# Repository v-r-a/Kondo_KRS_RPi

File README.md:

# Kondo_KRS_RPi
A Linux library for Raspberry Pi to operate the KRS motors (Kondo humanoid) using GPIO UART ports. 

Software dependencies: [wiringPi]([url](https://github.com/WiringPi/WiringPi)). wiringPi is needed for toggling RX/TX/En using the tri-state buffer.

Hardware dependencies: PCB for half-duplex communication with Kondo KRS 2552 motors.  The PCB designed is open-sourced here. However there are major changes in the PCB. A new version that is physically tested will be uploaded soon.

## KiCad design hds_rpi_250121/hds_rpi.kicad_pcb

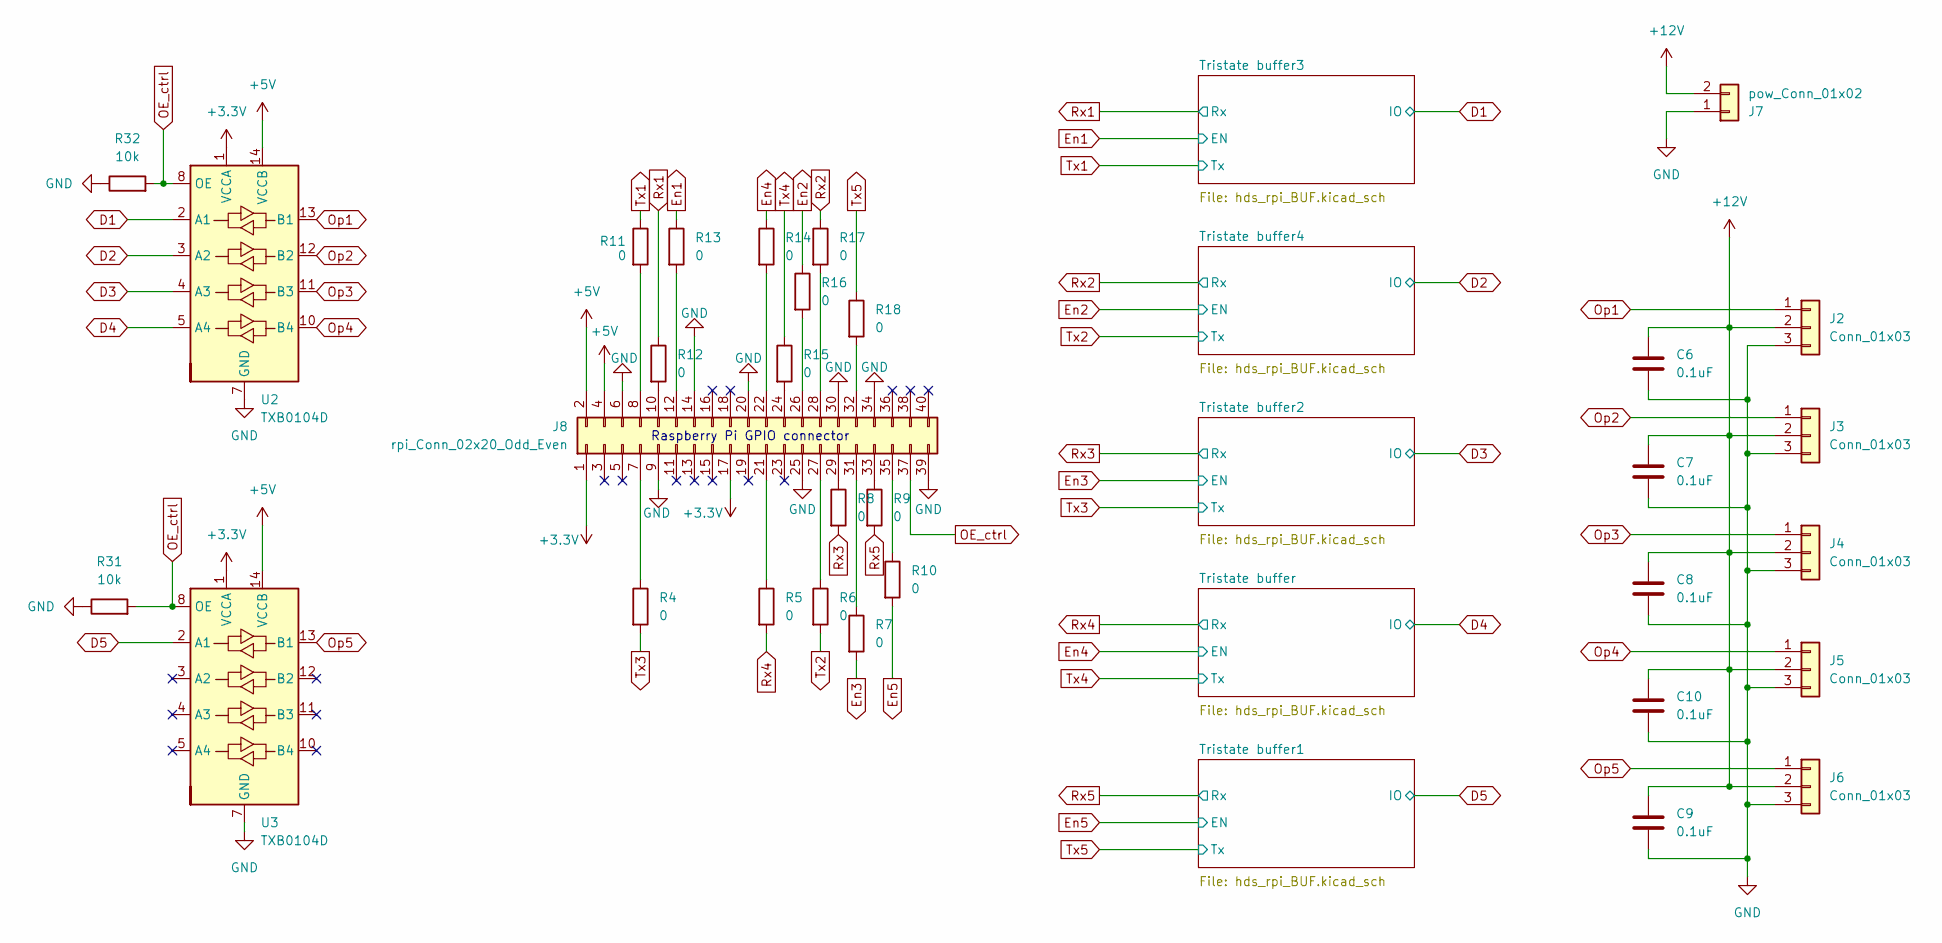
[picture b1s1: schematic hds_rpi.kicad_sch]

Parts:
C6, C7, C8, C9, C10: 0.1uF; L_1206_3216Metric_Pad1.22x1.90mm_HandSolder
J2, J3, J4, J5, J6: Conn_01x03; PinHeader_1x03_P2.54mm_Vertical
J7: pow_Conn_01x02; TerminalBlock_Phoenix_MPT-0,5-2-2.54_1x02_P2.54mm_Horizontal
J8: rpi_Conn_02x20_Odd_Even; Mirrored_PinHeader_2x20_P2.54mm_Vertical
R4, R5, R6, R7, R8, R9, R10, R11, R12, R13, R14, R15, R16, R17, R18: 0; R_1206_3216Metric_Pad1.30x1.75mm_HandSolder
R31, R32: 10k; R_1206_3216Metric_Pad1.30x1.75mm_HandSolder
U2, U3: TXB0104D; SOIC-14_3.9x8.7mm_P1.27mm

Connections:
+3.3V: J8.1, J8.17, U2.1 (VCCA), U3.1 (VCCA); also elsewhere on the board
+5V: J8.2, J8.4, U2.14 (VCCB), U3.14 (VCCB)
+12V: C6.2, C7.1, C8.2, C9.2, C10.2, J2.2, J3.2, J4.2, J5.2, J6.2, J7.2
D1: U2.2 (A1); also elsewhere on the board
D2: U2.3 (A2); also elsewhere on the board
D3: U2.4 (A3); also elsewhere on the board
D4: U2.5 (A4); also elsewhere on the board
D5: U3.2 (A1); also elsewhere on the board
En1: R13.1; also elsewhere on the board
En2: R16.1; also elsewhere on the board
En3: R7.2; also elsewhere on the board
En4: R14.1; also elsewhere on the board
En5: R10.2; also elsewhere on the board
GND: C6.1, C7.2, C8.1, C9.1, C10.1, J2.3, J3.3, J4.3, J5.3, J6.3, J7.1, J8.6, J8.9, J8.14, J8.20, J8.25, J8.30, J8.34, J8.39, R31.1, R32.1, U2.7 (GND), U3.7 (GND); also elsewhere on the board
unnamed: J8.7, R4.1
unnamed: J8.8, R11.2
unnamed: J8.10, R12.2
unnamed: J8.12, R13.2
unnamed: J8.21, R5.1
unnamed: J8.22, R14.2
unnamed: J8.24, R15.2
unnamed: J8.26, R16.2
unnamed: J8.27, R6.1
unnamed: J8.28, R17.2
unnamed: J8.29, R8.1
unnamed: J8.31, R7.1
unnamed: J8.32, R18.2
unnamed: J8.33, R9.1
unnamed: J8.35, R10.1
OE_ctrl: J8.37, R31.2, R32.2, U2.8 (OE), U3.8 (OE)
Op1: J2.1, U2.13 (B1)
Op2: J3.1, U2.12 (B2)
Op3: J4.1, U2.11 (B3)
Op4: J5.1, U2.10 (B4)
Op5: J6.1, U3.13 (B1)
Rx1: R12.1; also elsewhere on the board
Rx2: R17.1; also elsewhere on the board
Rx3: R8.2; also elsewhere on the board
Rx4: R5.2; also elsewhere on the board
Rx5: R9.2; also elsewhere on the board
Tx1: R11.1; also elsewhere on the board
Tx2: R6.2; also elsewhere on the board
Tx3: R4.2; also elsewhere on the board
Tx4: R15.1; also elsewhere on the board
Tx5: R18.1; also elsewhere on the board

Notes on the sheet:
Raspberry Pi GPIO connector

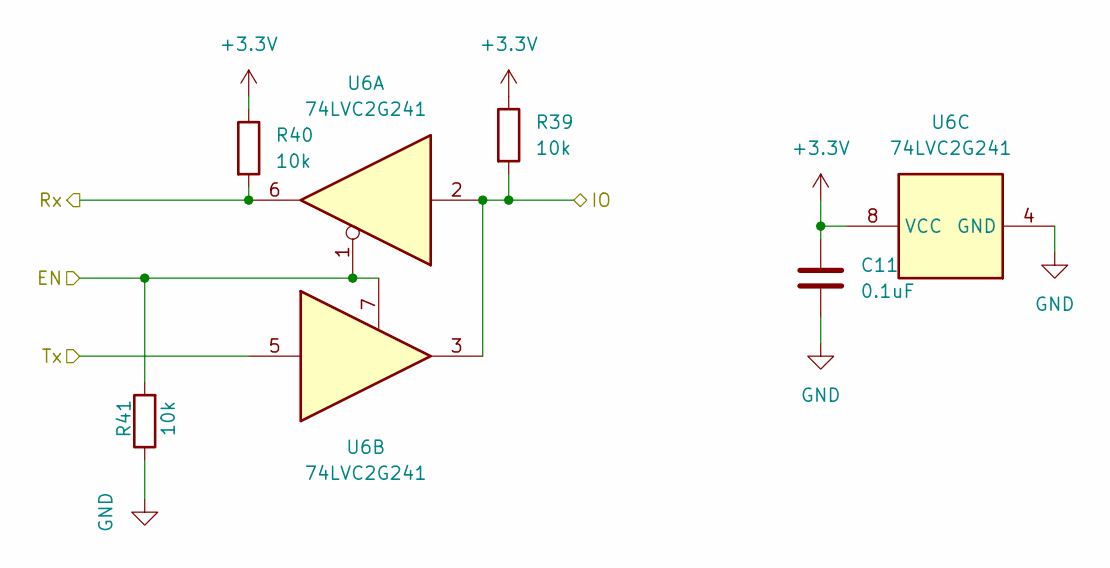
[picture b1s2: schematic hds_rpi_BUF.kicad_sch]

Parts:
C11: 0.1uF; L_1206_3216Metric_Pad1.22x1.90mm_HandSolder
R39, R40, R41: 10k; R_1206_3216Metric_Pad1.30x1.75mm_HandSolder
U6: 74LVC2G241; SSOP-8_2.95x2.8mm_P0.65mm

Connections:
+3.3V: C11.1, R39.1, R40.1, U6.8 (VCC); also elsewhere on the board
D4: R39.2, U6.2, U6.3; also elsewhere on the board
En4: R41.2, U6.1, U6.7; also elsewhere on the board
GND: C11.2, R41.1, U6.4 (GND); also elsewhere on the board
Rx4: R40.2, U6.6; also elsewhere on the board
Tx4: U6.5; also elsewhere on the board

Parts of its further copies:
C1, C2, C3, C4: 0.1uF; L_1206_3216Metric_Pad1.22x1.90mm_HandSolder
R1, R2, R3, R19, R20, R21, R22, R23, R24, R25, R26, R27: 10k; R_1206_3216Metric_Pad1.30x1.75mm_HandSolder
U1, U4, U5, U7: 74LVC2G241; SSOP-8_2.95x2.8mm_P0.65mm

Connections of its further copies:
+3.3V: C1.1, C2.1, C3.1, C4.1, R1.1, R2.1, R19.1, R20.1, R22.1, R23.1, R25.1, R26.1, U1.8 (VCC), U4.8 (VCC), U5.8 (VCC), U7.8 (VCC); also elsewhere on the board
D1: R19.2, U4.2, U4.3; also elsewhere on the board
D2: R22.2, U5.2, U5.3; also elsewhere on the board
D3: R1.2, U1.2, U1.3; also elsewhere on the board
D5: R25.2, U7.2, U7.3; also elsewhere on the board
En1: R21.2, U4.1, U4.7; also elsewhere on the board
En2: R24.2, U5.1, U5.7; also elsewhere on the board
En3: R3.2, U1.1, U1.7; also elsewhere on the board
En5: R27.2, U7.1, U7.7; also elsewhere on the board
GND: C1.2, C2.2, C3.2, C4.2, R3.1, R21.1, R24.1, R27.1, U1.4 (GND), U4.4 (GND), U5.4 (GND), U7.4 (GND); also elsewhere on the board
Rx1: R20.2, U4.6; also elsewhere on the board
Rx2: R23.2, U5.6; also elsewhere on the board
Rx3: R2.2, U1.6; also elsewhere on the board
Rx5: R26.2, U7.6; also elsewhere on the board
Tx1: U4.5; also elsewhere on the board
Tx2: U5.5; also elsewhere on the board
Tx3: U1.5; also elsewhere on the board
Tx5: U7.5; also elsewhere on the board

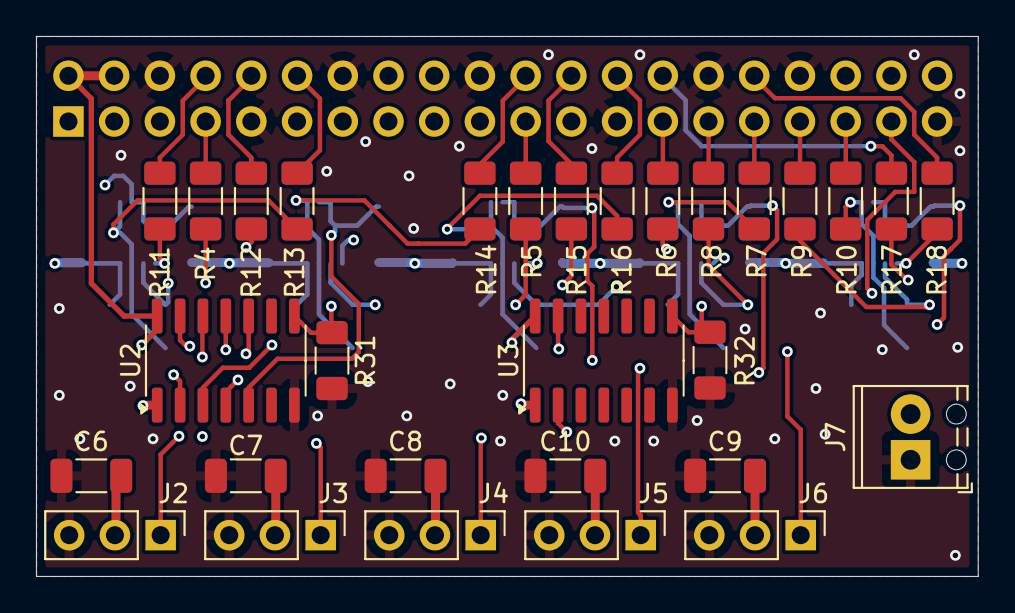
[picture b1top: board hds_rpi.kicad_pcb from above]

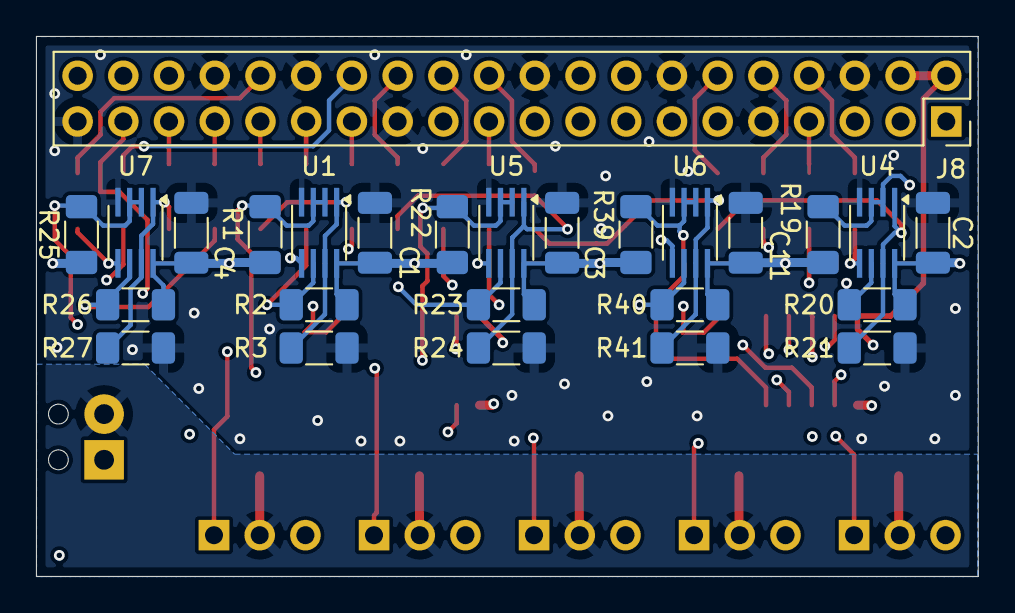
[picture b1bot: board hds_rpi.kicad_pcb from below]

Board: 4 copper layers, 52.3 x 30.0 mm, 56 parts (26 on the bottom side), 45 nets.

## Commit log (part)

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2025-05-04 PCB KiCAD files
